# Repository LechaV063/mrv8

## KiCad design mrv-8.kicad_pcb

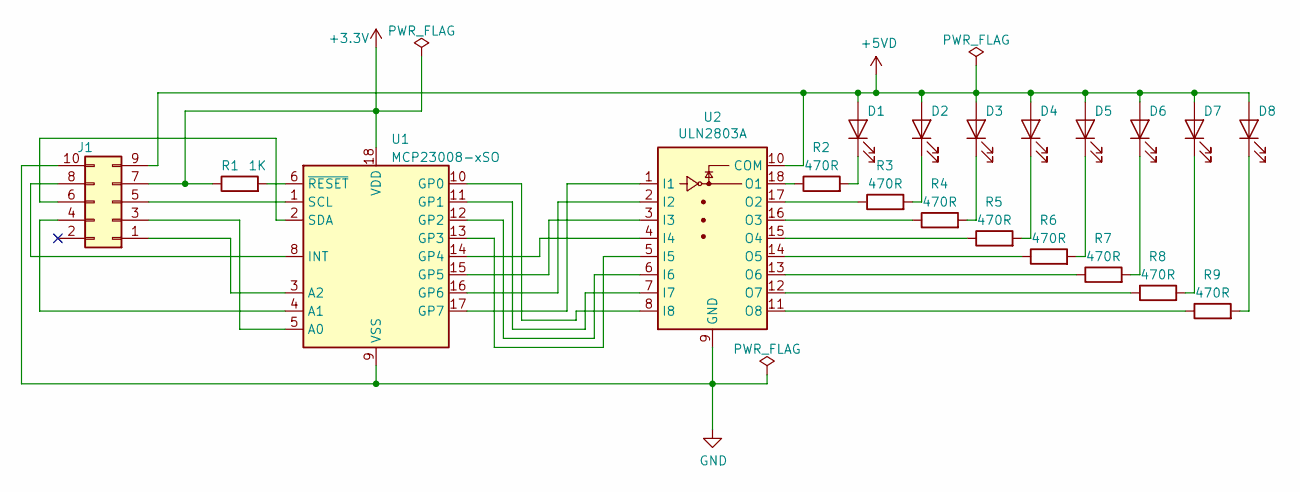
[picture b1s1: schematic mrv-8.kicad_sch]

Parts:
D1, D2, D3, D4, D5, D6, D7, D8: IR26-21C_L110_TR8; LED_1206_3216Metric_Pad1.42x1.75mm_HandSolder
J1: Conn_02x05_Odd_Even; PinHeader_2x05_P2.54mm_Horizontal
R1: 1K; R_1206_3216Metric_Pad1.30x1.75mm_HandSolder
R2, R3, R4, R5, R6, R7, R8, R9: 470R; R_0805_2012Metric_Pad1.20x1.40mm_HandSolder
U1: MCP23008-xSO; SOIC-18W_7.5x11.6mm_P1.27mm
U2: ULN2803A; SOIC-18W_7.5x11.6mm_P1.27mm

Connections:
+3V3: J1.7, R1.1, U1.18 (VDD)
+5VD: D1.2 (A), D2.2 (A), D3.2 (A), D4.2 (A), D5.2 (A), D6.2 (A), D7.2 (A), D8.2 (A), J1.9, U2.10 (COM)
GND: J1.10, U1.9 (VSS), U2.9 (GND)
unnamed: D1.1 (K), R2.2
unnamed: D2.1 (K), R3.2
unnamed: D3.1 (K), R4.2
unnamed: D4.1 (K), R5.2
unnamed: D5.1 (K), R6.2
unnamed: D6.1 (K), R7.2
unnamed: D7.1 (K), R8.2
unnamed: D8.1 (K), R9.2
unnamed: J1.1, U1.3 (A2)
unnamed: J1.3, U1.5 (A0)
unnamed: J1.4, U1.4 (A1)
unnamed: J1.5, U1.1 (SCL)
unnamed: J1.6, U1.2 (SDA)
unnamed: J1.8, U1.8 (INT)
unnamed: R1.2, U1.6 (~RESET)
unnamed: R2.1, U2.18 (O1)
unnamed: R3.1, U2.17 (O2)
unnamed: R4.1, U2.16 (O3)
unnamed: R5.1, U2.15 (O4)
unnamed: R6.1, U2.14 (O5)
unnamed: R7.1, U2.13 (O6)
unnamed: R8.1, U2.12 (O7)
unnamed: R9.1, U2.11 (O8)
unnamed: U1.10 (GP0), U2.8 (I8)
unnamed: U1.11 (GP1), U2.7 (I7)
unnamed: U1.12 (GP2), U2.6 (I6)
unnamed: U1.13 (GP3), U2.5 (I5)
unnamed: U1.14 (GP4), U2.4 (I4)
unnamed: U1.15 (GP5), U2.3 (I3)
unnamed: U1.16 (GP6), U2.2 (I2)
unnamed: U1.17 (GP7), U2.1 (I1)

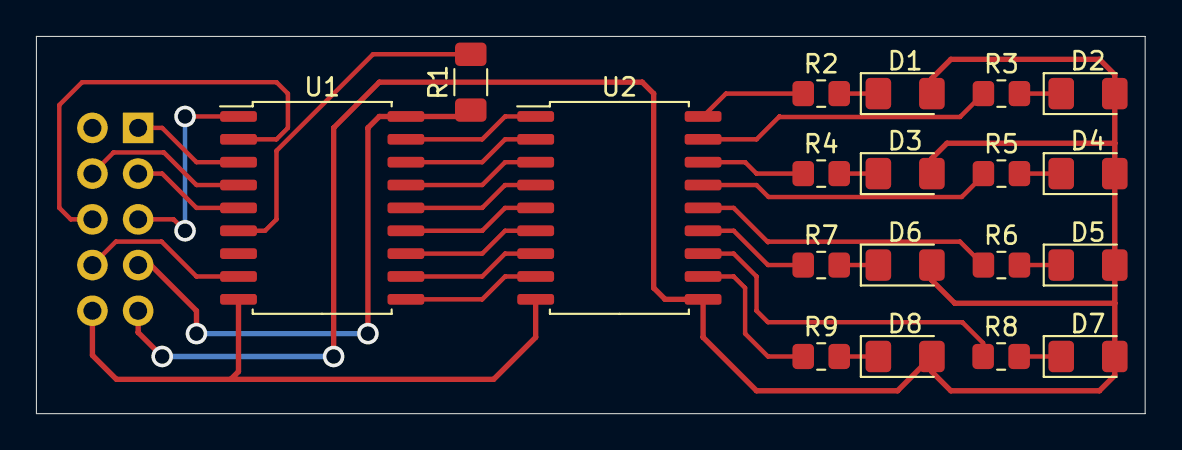
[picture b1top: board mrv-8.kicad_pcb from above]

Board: 2 copper layers, 61.6 x 21.0 mm, 20 parts (1 on the bottom side), 34 nets.

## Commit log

2022-07-20 edit pcb mrv-8
